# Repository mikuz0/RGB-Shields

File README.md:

# RGB-Shields
<p>RGB(W) шильд предназначен для создания прототипов и конечных устройств по управлению светодиодным освещением, совместно с Arduino nano.</p> 
</br>
<b>Основные характеристики: </b>

Напряжение питания: 12 в(ограничено Arduino nano) 

Выходной ток: не более 3 А на канал. 

Суммарный ток нагрузок не более 3 А. 

Количество независимых каналов: 4

Количество кнопок управления: 3

Возможность подключения ИК приёмника: да (приемник ИК сигнала vs1838)

Возможность программного контроля напряжения питания: да. 

Размеры габаритные: 60х49 мм

Размеры под винт: 52х38,4

3D модель: ссылка тут

Надписи с адресами подключения цепей на плате позволяют упростить создание программного обеспечения.

Демо ПО:

Есть пример, демонстрирующий основные возможности RGB(W) шильда. (<a href="https://github.com/mikuz0/RGB-Shields/tree/main/3d-print/models " >ссылка тут </a>) 

Пример предназначен только для проверки исправности RGB(W) шильда. 

Назначение кнопок в демоПО:

1. Переход на следующий режим

2. Увеличить яркость

3. Уменьшить яркость

Режимы демоПО:

1. Проверка совместной работы каналов. 

2. Проверка работы канала R. Остальные каналы закрыты. 

3. Проверка работы канала G.  Остальные каналы полностью закрыты. 

4. Проверка работы канала B. Остальные каналы полностью закрыты. 

5. Проверка работы канала W. Остальные каналы полностью закрыты. 

<b>Схема подключения RGBW-shield и данные для разработки програмного обеспечения.</b> <br>

<p>
Каналы R, G, B, W могут назначяться программно. В описании каналы обозначены в соответствии с предлагаемых ниже ПО. ПО не входит в поставку и предлагается как есть, без гарантий.
</p>

<p>
R - D3
</p>
<p>
G - D9
</p>
<p>
B - D10
</p>
<p>
W - D11
</p>

Каналы идентичный по нагрузочной способности.
VS1838 - D2
Кнопки D4, D5, D6  (см. маркировку на плате рядом с каждой кнопкой)

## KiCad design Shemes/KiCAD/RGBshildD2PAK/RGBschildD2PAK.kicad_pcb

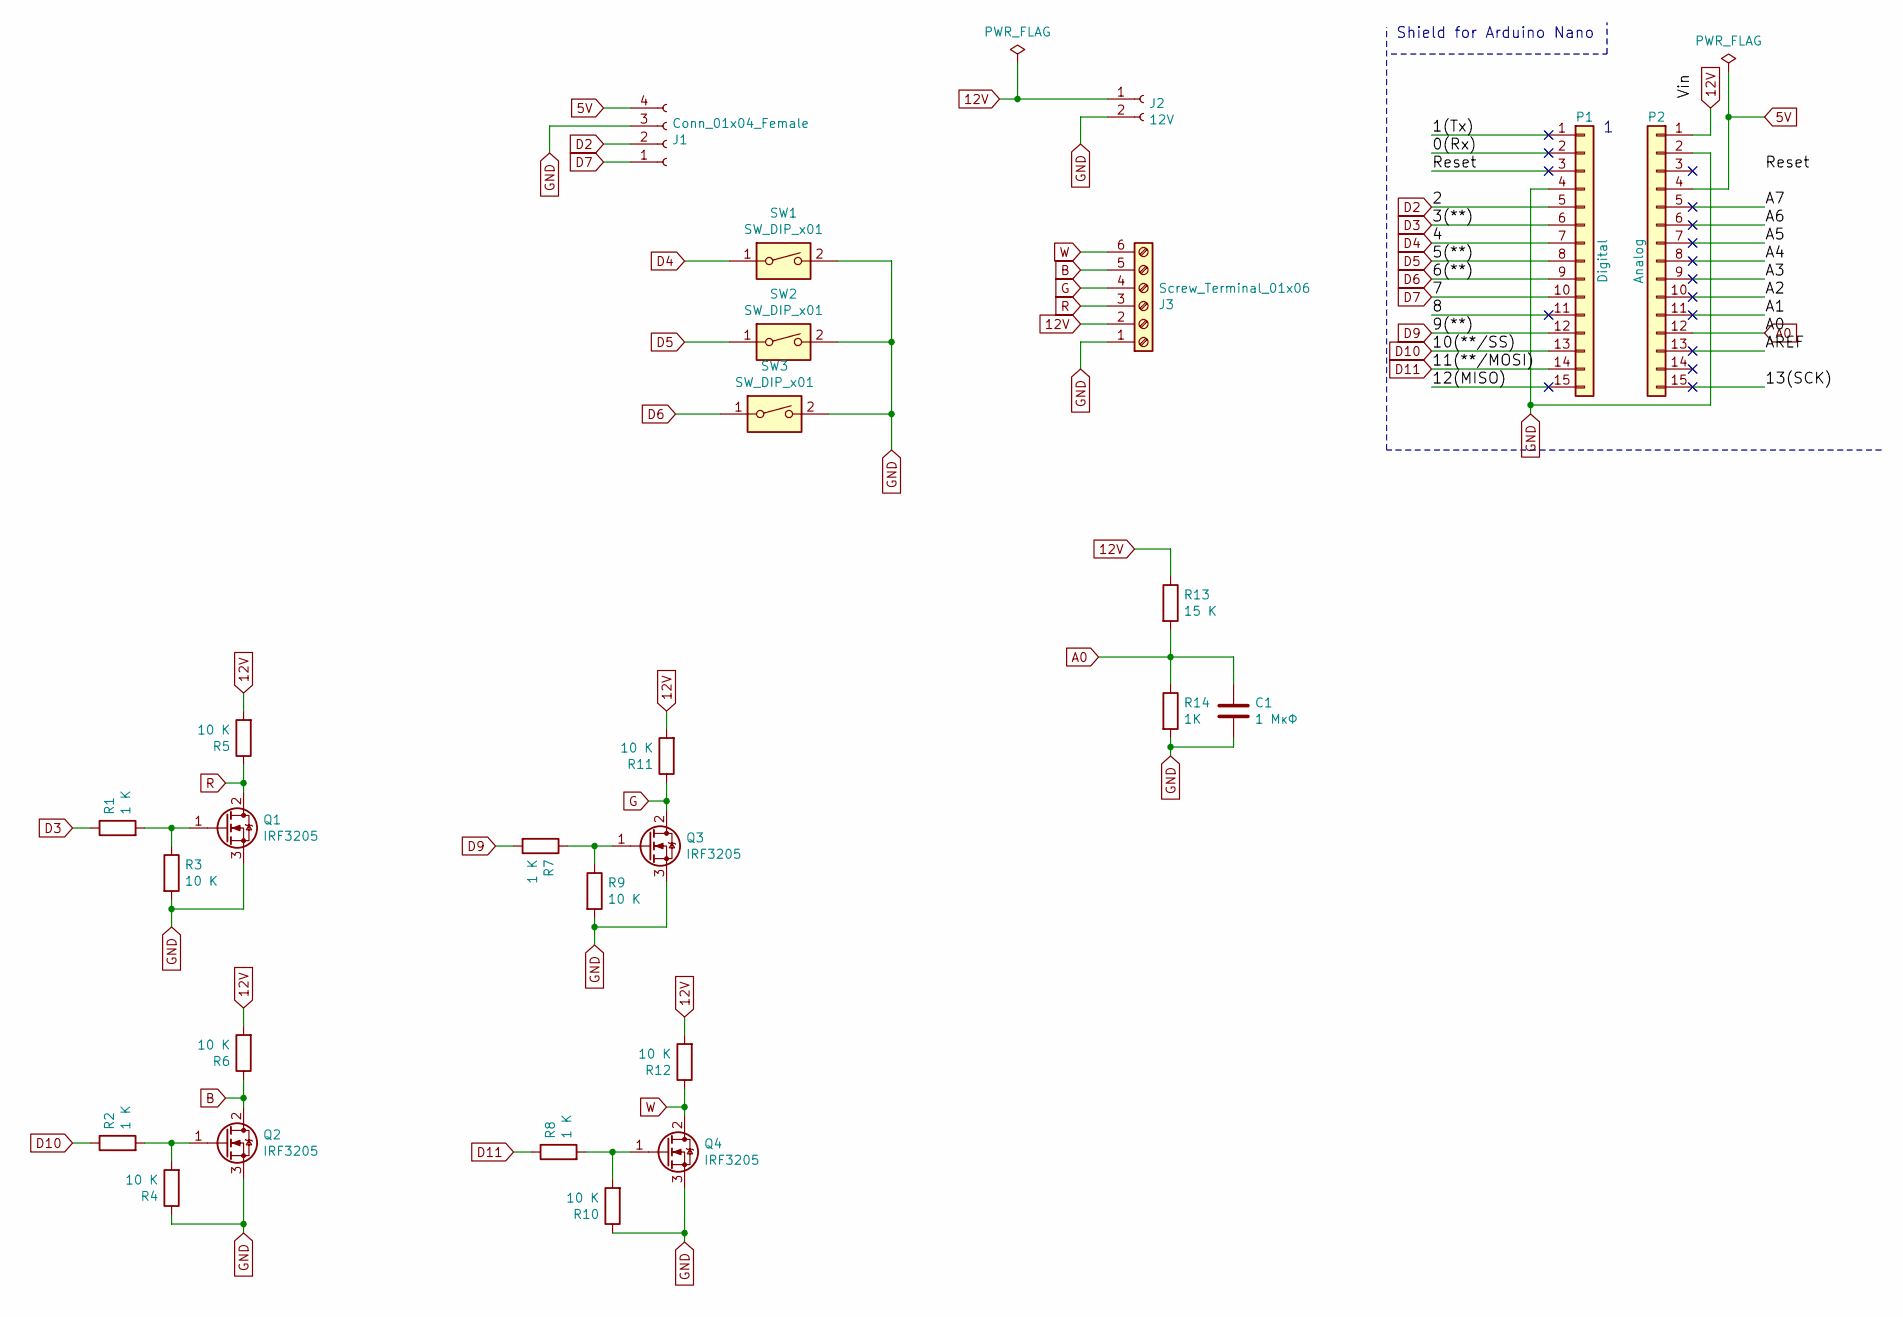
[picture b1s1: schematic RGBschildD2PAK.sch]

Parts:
C1: 1 МкФ; C_0805_2012Metric
J1: Conn_01x04_Female; PinSocket_1x04_P2.54mm_Vertical
J2: 12V; BarrelJack_Horizontal
J3: Screw_Terminal_01x06; TerminalBlock_Phoenix_PT-1,5-6-5.0-H_1x06_P5.00mm_Horizontal
P1: Digital; PinSocket_1x15_P2.54mm_Vertical
P2: Analog; PinSocket_1x15_P2.54mm_Vertical
Q1, Q2, Q3, Q4: IRF3205; D2PAK_12
R1, R2, R7, R8: 1 K; C_0603_1608Metric_Pad1.08x0.95mm_HandSolder
R3, R4, R5, R6, R9, R10, R11, R12: 10 K; C_0603_1608Metric_Pad1.08x0.95mm_HandSolder
R13: 15 K; C_0603_1608Metric_Pad1.08x0.95mm_HandSolder
R14: 1K; C_0603_1608Metric_Pad1.08x0.95mm_HandSolder
SW1, SW2, SW3: SW_DIP_x01; SW_PUSH-12mm

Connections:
5V: J1.4, P2.4
12V: J2.1, J3.2, P2.1, R5.2, R6.2, R11.2, R12.2, R13.1
/0(Rx): P1.2
/1(Tx): P1.1
/8: P1.11
/12(MISO): P1.15
/13(SCK): P2.15
/A1: P2.11
/A2: P2.10
/A3: P2.9
/A4: P2.8
/A5: P2.7
/A6: P2.6
/A7: P2.5
/AREF: P2.13
/Reset: P1.3
A0: C1.1, P2.12, R13.2, R14.1
B: J3.5, Q2.2 (D), R6.1
D2: J1.2, P1.5
D3: P1.6, R1.1
D4: P1.7, SW1.1
D5: P1.8, SW2.1
D6: P1.9, SW3.1
D7: J1.1, P1.10
D9: P1.12, R7.2
D10: P1.13, R2.1
D11: P1.14, R8.1
G: J3.4, Q3.2 (D), R11.1
GND: C1.2, J1.3, J2.2, J3.1, P1.4, P2.2, Q1.3 (S), Q2.3 (S), Q3.3 (S), Q4.3 (S), R3.2, R4.1, R9.2, R10.1, R14.2, SW1.2, SW2.2, SW3.2
unnamed: Q1.1 (G), R1.2, R3.1
unnamed: Q2.1 (G), R2.2, R4.2
unnamed: Q3.1 (G), R7.1, R9.1
unnamed: Q4.1 (G), R8.2, R10.2
R: J3.3, Q1.2 (D), R5.1
W: J3.6, Q4.2 (D), R12.1

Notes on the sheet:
Shield for Arduino Nano

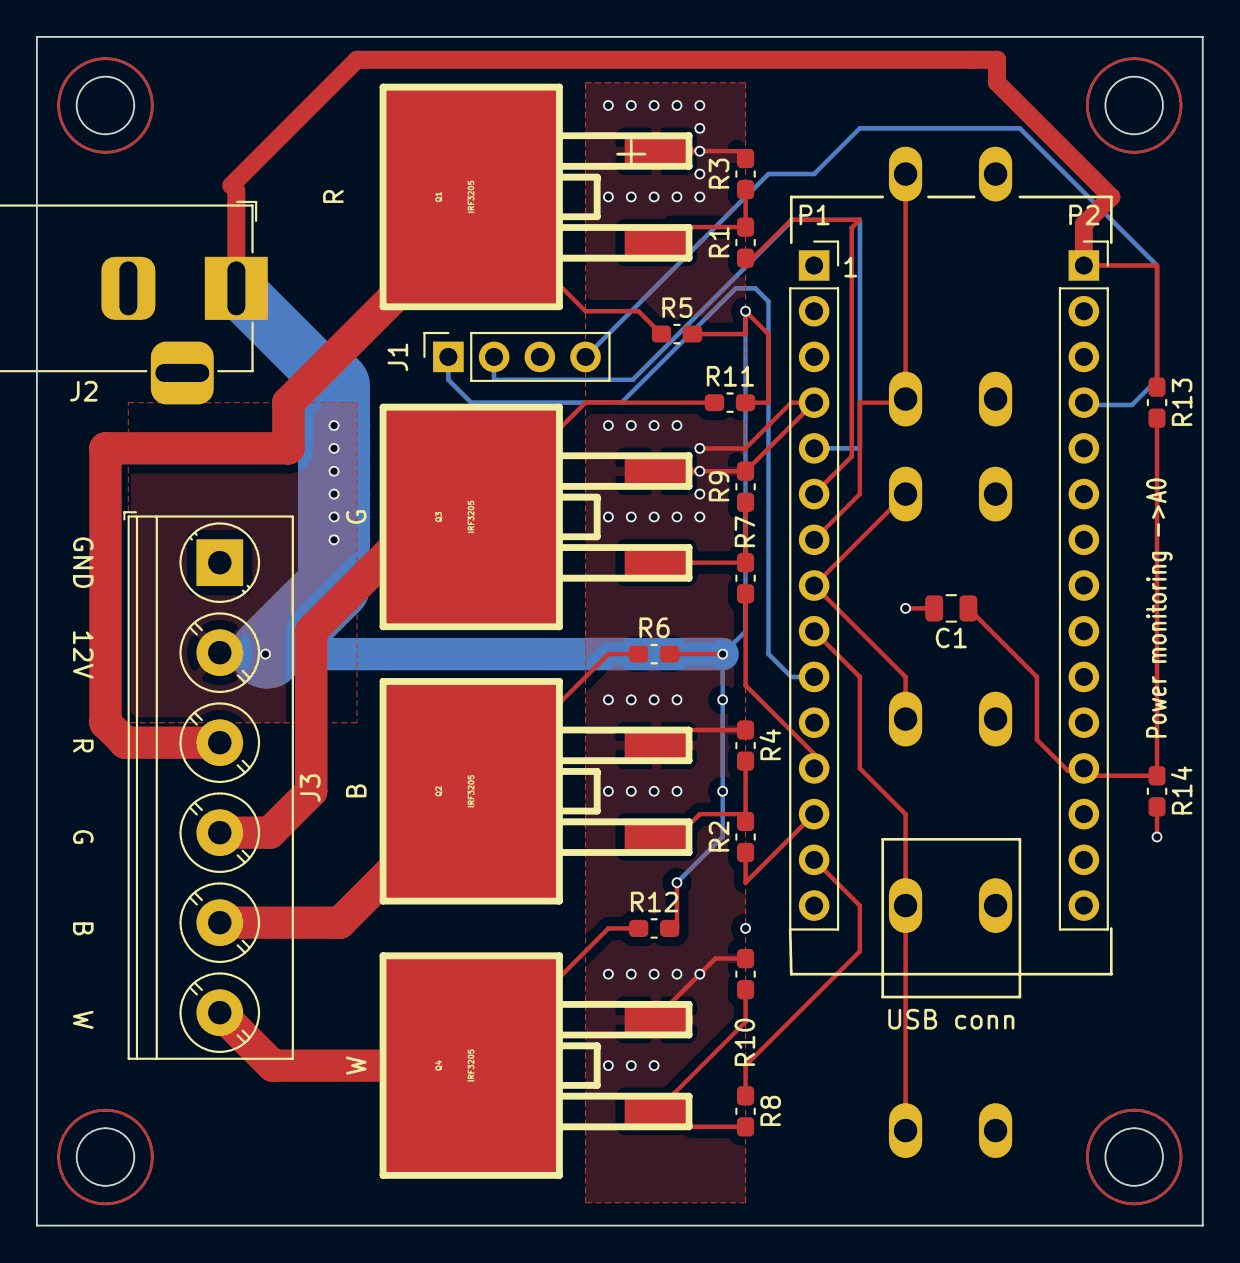
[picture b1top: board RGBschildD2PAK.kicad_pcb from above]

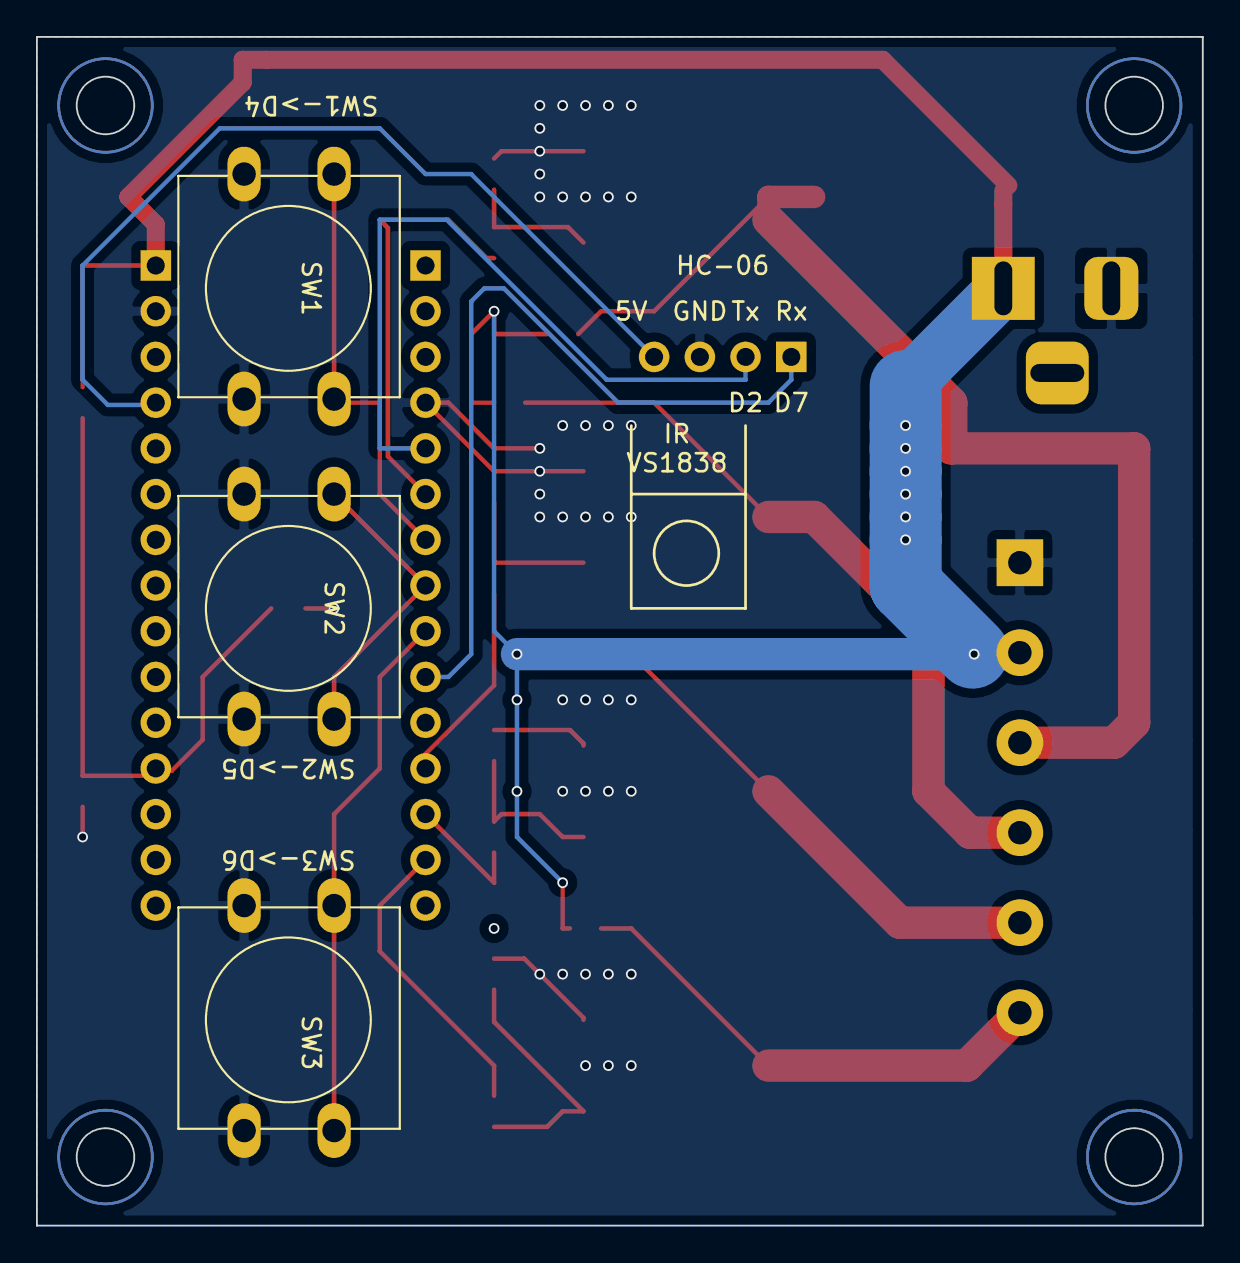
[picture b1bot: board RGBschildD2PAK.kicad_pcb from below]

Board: 2 copper layers, 64.8 x 66.0 mm, 27 parts (3 on the bottom side), 21 nets.

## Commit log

2021-10-05 Proba
2021-10-13 usermanual
2021-10-16 case
